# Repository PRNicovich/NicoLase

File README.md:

# NicoLase 

## An open-source diode laser combiner, fiber launch, and sequencing controller for fluorescence microscopy

New users please check out the associated open-access publication from PLoS ONE:
http://dx.doi.org/10.1371/journal.pone.0173879

Therein you'll find a complete description of the NicoLase platform and performance specifications.  

Here in the repository you can find all of the files and supplementary descriptions to build your own fiber-coupled diode laser launch as described in the publication. As the project matures, new features and softwares will be incorporated here.  

### Motivation
Diode laser units are convenient for fluorescence microscopy and super-resolution microscopy due to their high power and ease of use.  A couple dozen lines are avaliable from most makers to cover UV through mid-IR applications.  With the addition of direct modulation avaliable on nearly all modern units there's no need for an AOTF or other tuning or power modulation control in addition to the diodes themselves. 

Multiple laser lines are almost are a requirement for a modern fluorescence microscope.  Rarely can a system produce publication-appropriate results without at least a second laser.  Multiple lasers need to be combined and then controlled together for multicolor illumination.  

Software and trigger control of the lasers is strongly desired.  Microscopy cameras often have a dead time between frames when laser illumination is (almost always) undesired, and at the very least it's nice to have a laser that shuts off when the acquisition simply isn't running. Then, as a further step, it's often necessary to alternate or otherwise sequence lasers for certain experiments (*ie* ALEX FRET or pseudo-simultaneous multicolor imaging).  With digital control of laser emission this needs to be controlled at the laser head. 

There are commercial options to achieve nearly all of these.  Basically, this system does not do anything you can't buy.  But the final cost here is 2/3 to 1/2 of the cost of commerical instruments and can be easily customized in terms of size, number of lines, and final configuration.  The system here is cheap (ish), flexible, and quite compact. 

Two generations of this project are included in the repo.  The first, half-sarcastically called the NicoLase 1500, is a single-mirror coupling system running 5 (expandable to 6) diode lasers.  The later, the NicoLase 2400, is a two-mirror system with 4 diode lasers.  These share the same footprint, many of the same components, and the same control software and PC interface.  

Note: Throughout I use the catch-all term 'lasers' or 'laser outputs' for the end target for TTL outputs of the controller.  Of course this same controller and software can be used with any equipment receiving a TTL input pulse that needs to be synced to camera acquisitions.  We commonly use an LED illuminator for transmitted light with the controller output, for example. 

### Hardware
#### Lasers
The NicoLase is built primarily around Vortran Stradus laser diode units.  These are a standardized size for each line, reasonably priced, and produce a large amount of power for their size and cost.  Nearly all produce enough power for dSTORM work.  These units can be digitally modulated at a high rate (usually up to 2 MHz) and potentially analog modulated if desired.  I don't have any financial reason for recommending these units, just a satisfied customer.

A straightforward modification allows you to use Coherent OBIS heads in place of some/all of the Vortran units.  Control is nearly identical and aside from some extra screw holes, these are drop-in replacements for the Vortran units. 

I haven't had a chance to test any other laser diodes with this system, though there's no reason others with the same characteristics won't work.  

Key features for any lasers chosen are :  
-  100 mm x 50 mm footprint or smaller
-  19.05 mm or 3/4" beam height, or can be brought to this height with spacers/lifts
-  Digital modulation via TTL pulse
-  Software control of laser power via USB or RS-232 (for add-on plug-in control)

#### Heatsinks and Mounting
Diode laser heads require a heat sink for proper operation, which has to at least be a contact with a block of aluminum.  We need the laser outputs to be at 39.0 mm to intersect with the steering and coupling optics.  Oh, and the laser have to actually bolt down to something. 

To solve these issues, a heat sink + mounting block was machined.  Three dimensions must be held to strict tolerances for this part.  The top must be as flat as possible (0.1 mm specified) with no scratches or machine marks to interface with the bottom of the laser diode for heat transfer.  The top and bottom faces must be parallel (0.1 mm specified) so the beams are at the same height.  And the total height must be the specified thickness (0.2 mm specified).  

Keeping the top flat can be done by using a piece of ground stock and machining other faces.  Keeping the top and bottom flat to that tolerance should be straightforward for a decent mill.  And we can use a bit of a trick for the total height.  This is because we don't actually care about the bottom of the part and can therefore add shims of sheet stock (with clearance holes cut) to bring the total assembly to the desired height.  The block can be machined on the bottom face until the thickness is a bit short, then a piece or pieces of sheet stock selected to bring it up to the final thickness.  Much simpler and easier to meet the necessary tolerance than hitting the right thickness with machining only.  

The heat sink block must be made of either aluminum or copper.  Steel, especially stainless, does not have a sufficient heat transfer rate to keep the diodes from overheating.  We had our top blocks made from aluminum and the shims from copper sheet, which works great. DO NOT add heat sink paste or thermal grease to the interface between the laser and the heat sink block.  That stuff outgasses like mad and gets on your optics, plus the flat surface does an excellent job of heat transfer already. 

Mirrors and other optics mount to standard Thorlabs parts except for the fiber coupler itself.  This needs a custom pedistal to be machined, but this is a straightforward piece of turning.  No dramas there.  The original 1500 design uses a flat block for this mount but the 2400 pedistal is a much better design. 

All optics are chosen for a 1.5" center height.  Mirrors and dichroic mirrors are mounted in Thorlabs Polaris 1" mounts.  The single-mirror system requires 3-adjuster mounts, but either 2- or 3- adjuster mounts can be used for the two-mirror system.  Hex adjuster are nice for squeezing the mounts closer together, but are a bit more of a pain to adjust.  Clearances are just barely there for thumb adjusters and for your fingers. Those more rotundly-digited of us may prefer the hex adjuster mirrors.  

Excitation filters can be mounted in standard lens mounts, or options for 3D printed mounts for 1/2" filters designed for the NicoLase is given in my 3D printing repo [here](https://github.com/PRNicovich/3D-Printed-Optics-Lab-Parts).  A mount to tie the Aruino to the optical table is given in the same repo, or you can make a mounting plate to bolt in a spare laser slot on the heat sink block (3D printed version forthcoming).  

Drawings and pictures of enclosures are provided (one a bit more 'polished' than the other).  These keep the lasers away from the unsuspecting eyes of users and the optics protected from bumps and dust.  Components for the NicoLase 1500 enclosure are from 80/20 using 25 mm aluminum profile.  The 2400 enclosure is made of corrugated plastic sheeting and held together with magnets and 3D printed magnet clips (available [here](https://github.com/PRNicovich/3D-Printed-Optics-Lab-Parts/tree/master/Magnet%20Clips)).  In both cases the laser power supplies are on the optical table with the breadboard and lasers above, but there's no reason the whole assembly can't be moved to a shelf off of the optical table if you need the space.  

**Update April 2019** - Plans for an enclosure in the form factor of a 19" rack (that fits under the optical table!) is included in 3600 model folder.  This rack can hold the NicoLase breadboard in the upper compartment with additional accessories and equipment underneath. This includes laser power supplies (on their own shelf) with any additional boxes, power supplies, or even a PC underneath.  Laser portion can be enclosed for a facility or dark room application.  Whole thing sits on sliding feet to fit under the optical table making a very convenient package! 

Technical drawings for all machined components are given.  These were sufficient for our Uni's machine shop to complete satisfactory work with no additional consultation.  

#### Optics
Optics are relatively straightforward - a few dichroic mirrors, optional filters, and a fiber coupler.  This unit is built around mostly standard Thorlabs components.  Aside from a T-shirt I got at a conference once, I have no interest in pushing Thorlabs components though they are reliable, self-compatible, and widely available. 

Dichroic mirrors are used to combine lasers into a single multi-wavelength beam.  A mix of Chroma and Semrock filters are used.  All are standard 1" round long-pass filters costing a few hundred USD each.  Which ones are used depends on which wavelengths are being combined, but of course you want to pick a cut-on wavelength that reflects the beam being folded in and transmits all others upstream.  Picking a cut-on wavelength that falls between adjacent laser lines usually works well, but double-check the provided spectra to confirm there aren't odd peaks or dips in the filter spectrum.  

Diode lasers often require an emission clean-up filter to block odd long-wavelength emission from the laser head.  We've had particularly bad luck with 488 nm diodes in this sense.  At the same time, diode heads are ordered by nominal wavelength, but the actual wavelength of the supplied unit may vary 3-5 nm from this nomial value.  This means that you can't necessarily order a laser line filter for the nominal wavelength and have it work for your diode.  For example, our '488' nm diode actually emits at 490 nm, and our 488 nm clean-up filter blocks half of the emitted power.  A 485/10 band-pass filter does a much better job and blocks the offending green emission.  This means you MUST double-check the actual emitted wavelength (should be specified by the vendor in the factory testing docs) when chosing an emission filter or if emitted wavelength is critical. 

A Thorlabs PAFA-X-F-A Achromatic FiberPort FC/APC coupler is used to couple the combined laser beams into a polarization-maintaining FC/APC patch cable.  The FiberPorts aren't cheap (~$500 USD), but they do prove to be stable and relatively achromatic.  50-70% coupling efficiency across all lines is achievable without too much hassle on this configuration.

A bill of materials for optical components is given in the Hardware folder of the repo.  

A procedure for the assembly and alignment of the optics has also been included in the Hardware\Optics\ folder of the repo.

###### One mirror or two?
Using two mirrors to steer a beam from one vector to another is taken as dogma for most applications. It is true that this is necessary for arbitrary output and input vectors, but that's not the case here.  

Because lasers with identical beam heights and angle relative to the breadboard are used (assuming proper machining tolerances on the mounting block), one degree of freedom is removed. As such you don't need four adjusters to steer the beam into the fiber coupler, but rather three.  This means that you can use a single three-adjuster mirror mount and, as a result, squeeze 6 laser heads and steering optics into a single 450 mm x 300 mm footprint.  Alignment of a single-mirror system is only marginally more difficult than aligning the two mirror system. This layout is given in the NicoLase 1500 description.  

A more typical two adjuster layout is used in the NicoLase 2400.  This uses a pair of two-adjuster mirrors for each laser and fits four lasers into the 450 mm x 300 mm footprint.  Using two mirrors does have more tolerance for lasers that might have unequal beam heights, such as when mixing Vortran and OBIS diode heads in a single unit. 

**Update April 2019** - A new, improved, 6 head version included as NicoLase 3600.  This combines the loads of lasers in the 1500 (plus an one more!) with the ease of alignment of the 2400.  The use of new Thorlabs 12 mm posts and 1/2" optics squeezes an additional mirror path in the same footprint as the other NicoLase designs.  The resulting design is easier to align and support combinations of laser makers who might have slightly different opinions on what a 3/4" beam height actually is.  This breadboard design is also a bit taller (1.6" inches vs 1.5"; 39.3 mm vs 38.1 mm) with a to avoid the need of any additional custom-made mounting components beyond the heat sink.  This combined with the new rack mount enclosure is a compact, easy to align, integrated solution for your microscope hardware. 

An additional 5-head version of the heat sink is included (NicoLase 3500) that allows additional beam conditioning or steering accessories to be included on the breadboard.  Like the 3600, there is a 39.3 mm beam height, dual mirror alignment on the fold-in lines, and fits well in the 19" rack style enclosure.

Special thanks to Mike Taormina for the clever design.

#### Controller
Trigger translation, especially with a time-variable component, requires some form of controller.  A DAC board (such as the many options from National Instruments) are the "professional" choice, but are frankly overkill.  A couple of input channels and no more than 8 input channels are needed. Timing precision, rise times, and trigger jitter on the microsecond or even tens of microseconds time scale is actually more than good enough here (10 microseconds of jitter on a 10 ms exposure is a 0.1% variation). USB or serial control is good to communicate with the controller,  as is low cost for the unit and the I/O interface.

Enter the Arduino Uno.  Units cost $40 AUD for an official one (knock-offs are under $10).  Timing precision and programming space is sufficient, I/O interfaces are easy with a shield, and there's a USB serial port built-in.  

Another Arduino variant or another microcontroller can be swapped in if the need arises (maybe you want to add more analog ins/outs? or a 32 bit timer?) but that's beyond the scope of this project.  As long as you can take a master trigger in, output the appropriate pulses, and communicate over a serial port, this part can be modified to meet your needs.

Interfacing with the trigger pulses in and out is accomplished with a custom shield.  The PCB includes 10 BNC ports (2 camera inputs, 2 camera outputs, and 6 laser outputs), a OR gate, 3v3 to 5v level shifter, and pushbutton, plus a few pull-down and limiting resistors.  With some male header strips, the shield mounts atop the Arduino.  

Circuit schematic included in ShieldPCB folder.  All power is drawn from Arduino.  PRIMARY TRIGGER camera input heads straight to SECONDARY TRIGGER output as well as to a 3v3 OR gate.  Other OR gate input is SECONDARY FIRE input, meaning either camera can be used to trigger Arduino.  OR gate output connects through 4050 3v3->5v level shifter to ensure that pulse adequately triggers 5v input on Arduino.  There the 5v pulse connects to interrupt digital pin 2 of the Arduino.  Arduino digital pin 3 connects to pushbutton on PCB which can also be used to iterate laser sequence for testing in place of a camera trigger.  Digital pin 4 goes through a current-limiting resistor to the PRIMARY TRIGGER output. 

All CHX outputs occur on Analog Out register of Arduino.  Sharing a register means all can be set simultaneously in the Arduino software without having to go through the digitalWrite() function.  This allows faster triggering and all lasers are set with the same delay/jitter rather than a variable delay depending on which pin on the register they lie.  

The shield PCB can be ordered [here](https://dirtypcbs.com/store/designer/details/8887/5815/nicolase-arduino-shield-v2-1).  If you order there I get a dollar or two of shop credit, but you're welcome to take the files in this repo and order them from another supplier.  A bill of materials is also included in the Shield repo for the parts necessary to populate the shield.  Surface mount components are used to get everything squeezed into the space available.  These may be small but they can be successfully hand-soldered using a standard temperature controlled soldering iron and reel solder.  A great guide for those getting started with surface mount components is available from SparkFun (https://www.sparkfun.com/tutorials/36). All should be commonly available from standard suppliers (element14, Mouser, DigiKey...) though I haven't done any work to ensure the longevity of the supply chain for any specific component.

### Software
Software is split into two parts - controller software running on the Arduino and interface software for the PC.  Only the controller software is strictly necessary for triggering.  Examples of PC software are given which can be expanded to work with your particular system.

###### Controller Software
The Arduino sketch accomplishes two primary needs - external communication and sequence programming via serial port, and triggering + interating a programmed laser sequence in response to a trigger pulse.  

Serial commands are via the USB connection to the control PC.  This USB also provides power to the Arduino, so no additional external supply is required.  Once powered on, the Arduino listens over the serial port for an incoming sequence to alter the standard sequence (all lasers on when the fire signal is high) or to reach any of the alternate features.  

A detailed description of the possible serial commands is given in the documentation in the Arduino Sketch folder of the repo.  Breifly each command is a capital letter character, sometimes a space followed by one or more digits, and a newline character.  

A Basic Controller and an Advanced System Controller are included in the repo.  The Basic Controller relies on an external trigger signal (ie a camera Fire pulse) to synchronize and iterate over the sequence of outputs.  The Advanced System Controller provides the main features of the Basic Controller in external clock mode, but additionally can be configured to have the Arduino act as the master clock for the system. 

The Basic Controller is simpler to operate and is sufficient for most applications.  The Advanced System Controller is a great option if you wish to have a master clock that isn't reliant on the camera signal.  Additionally, the Advanced System Controller solves the timelapse issue in Micromanager for acquisitions between ~3 Hz and the free-run rate of your camera.  More detail on this issue is given below.

Both configurations use the same hardware and share many of the same serial commands. Switching between the two options is a matter of uploading the appropriate sketch to the Arduino and intefacing with the respective PC-side software or serial commands.

###### Basic Controller

Triggering (via either the PCB PIMARY FIRE or SECONDARY FIRE connection) triggers an interrupt on the Arduino. A rising edge causes the laser outputs (CH1 through CH6) to go high.  A falling edge on the trigger pulse drives the laser outputs low and iterates the programmed sequence to the next one.  If the end of the sequence list is reached the Arduino goes back to the start.  Any given line of the sequence can be repeated any number of times (up to 2147483647 times per line).  

Alternate functions are available for what is called a pre- or post-acquisition command.  These are single laser patterns that can be triggered by a serial command independent of a trigger input.  Each has a time associated for how long the outputs will be held high.  The pre-acquisition sequence has an additional delay after which an optional pulse will be send to the PRIMARY TRIGGER pin.  This means you can, for example, have an acquisition sequence of a 488 nm laser and 561 nm laser firing on alternating camera frames (the 'acquisition sequence').  Before that sequence is reached, however, a pre-acquisition sequence of a 405 nm laser is fired with no camera acquisition for 1000 ms, followed by a 500 ms delay, and then the actual acquisition begun by the Arduino sending a pulse to the primary camera.  A more detailed description of the 
triggering and associated controller functions is given in the Triggering section.  

Additional commands enable configuration of the controller as a UserDefinedStateDevice and UserDefinedShutter device in Micro-Manager.  In this mode basic fluorescence microscopy functions (select a laser set and toggle on/off) directly through Micro-manager GUI.  For those wishing to use the NicoLase in a straightforward or multi-user environment this may be useful. 

###### Advanced System Controller

The basic controls for laser sequencing during a camera-synchronized acquisition described above are supported.  In addition there is an available mode in which the Arduino can act as the master system clock.  The camera and lasers are then both driven by the Arduino system clock.

The primary motivation for the Arduino as the master clock is solving the no-mans-land of timelapse rates between the camera's free-run rate (delay < [exposure time + dead time]) and ~3 Hz.  In Micromanager, the timelapse delays in this range seem to change from a continuous camera acquisition to a series of single acquisitions at a given rate.  This comes with much more communication overhead, ultimately limiting the capture rate to accomodate the ~250 ms of added delay. Such a delay is not immediately obvious in the software without checking the timestamps of acquired images and may not necessarily affect your system or measurements. We like to work in the affected range for our system, however, so a solution is needed.  

In this configuration all cameras are set to External Trigger mode.  The primary camera is then triggered by the Arduino.  If a secondary camera is present, it is triggered by the Fire signal from the primary camera.  By having all cameras set to External Trigger mode, the communication overhead comes once at the beginning of the acquisition.  Between frame captures the camera does not have to communicate with the PC except to transfer image data.  The cameras wait for the next incoming external trigger pulse to take the next image and are able to capture without additional communication overhead.  This means timelapse images can be captured at any rate from the free-run rate of the camera on up to a limit imposed by the Arduino timing roll-over (days to weeks).  

It is essential that these external pulses come when the camera is listening, so the external delay must be greater than the set exposure time plus the camera dead time (50-65 ms on an Andor 888; check the Minumum Cycle Time on the Micromanager Device Property Browser for this value).  The current version of this software does not check for a 'Ready' signal from the camera before sending the next pulse, so this timing is the responsibility of the user. 

** Note ** 
With the Arduino as the master clock, you don't need another clock signal!  If you simply want to trigger TTL devices at a given rate, then this software may work for you!  See .\Software\AdvancedSystemController\Arduino_controller documentation for details on how to control sequencing and serial communication with the associated Arduino sketch.

###### PC Software
Communication with the Arduino is through standard serial commands.  Serial settings are essentially defaults - 9600 baud, 8-n-1, and a newline character line feed.  

The Arduino is added to the Micro-manager config as a FreeSerialPort device (be sure to get the right COM port + settings!) for this communication.  sendSerialPortCommand() calls pass along strings to the Arduino at the beginning of the experiment (or during, if you want) which then waits for trigger pulses from the camera.  

For the Basic Controller an example Micro-manager script to communicate laser sequence settings are given for inclusion into the Beanshell interface.  A MATLAB GUI for easily uploading arbitrary sequences is also included.  This can run in parallel with Micro-manager if the FreeSerialPort has NOT been added to the Micro-manager config, or in your own external application. 

A Micro-manager plug-in for the Advanced System Controller includes a GUI for programming laser and camera sequencing as well as loop and step timing.  The configuration is passed to the Arduino via serial commands and the acquisition sequence begun.  The plug-in then reassembles the data sequence into the proper multidimensional stack, including separating channels by camera and laser configuration dimension.  

**Update March 2019** - The Basic Controller now supports use as a SerialStateDevice and SerialShutter in MicroManager.  This allows you to control the laser sequencer just like a physical shutter or filter wheel.  See the software build notes for details.

**Update May 2020** - Basic controller sketch can now be controlled via the nicoLase Python class.  Package is in ./Software/BasicController/Python.  Run "pip install -e ." with terminal pointed to that directory to install. 

### Triggering
A diagram of the triggering sequence in the default external clock mode is given below:

Here input signals are blue (Primary In and Secondary In), outputs to cameras in red (Primary Out and Secondary Out), and outputs to lasers in wavelength-approximate colors (Ch6 - Ch1).  Trigger event stages are separated by dashed black lines with acquisition frames in gray blocks with gray dotted borders.

Because the SECONDARY FIRE and PRIMARY FIRE inputs first pass through an OR gate, either being high results in the input to the Arduino being high.  In practice the separation between these two pulses is on the order of single microseconds, so these are treated as simultaneous.  Also, this means that even in a dual-camera system, running either camera alone is sufficient to trigger the CHX outputs.  Single cameras can work on either, though using PRIMARY TRIGGER input only is recommended.

The progression of trigger signals for this experiment of 8 imaging frames is as follows:
-  Serial command to Arduino starts Pre-acquisition sequence with Ch1 and Ch6 high (ie 405 nm laser and blue transmitted LED)
-  After defined illumination time, Pre-acquisition ends and Pre-acquisition delay begins
-  After defined pre-acquisition delay time, a pulse is sent to the PRIMARY TRIGGER output
-  The Primary camera begins acquiring frames (charcteristics defined through camera software).  Each is associated with an input pulse at the PRIMARY FIRE pin
-  Each incoming PRIMARY FIRE pulse results in an output SECONDARY TRIGGER pulse and output pulses to the user-specified CHX output pins.  Here I show alternating sequences of [Ch5 + Ch4] and [Ch3 + Ch2] to illustrate the programmable sequencing of these pins. 
- Each SECONDARY TRIGGER pulse triggers the secondary camera, which in turn results in an incoming SECONDARY FIRE pulse (ignored in 2-camera acquisitions)
- Falling edge of PRIMARY FIRE pulse drives CHX outputs low and Arduino iterates to next line of sequence
- After acquisition is complete, serial command to Arduino starts Post-acquisition sequence (here Ch6, blue transmitted LED high) for user-defined time

With the Arduino as the master clock, the primary camera follows trigger pulses from the Arduino.  The secondary camera, if present, follows the primary camera.  For each frame the PRIMARY TRIGGER pin on the Arduino is used to trigger the primary camera, which is in External Trigger mode (rather than External Start or Software triggering).  The Advanced Laser Controller software does not explicitly support a Pre- or Post-acquisition exposure at this time.

Outgoing pulses are all 5v TTL.  Incoming signals are anticipated to be 3v3 TTL signals (5v tolerant).  

Typical configuration assumes that CHX outputs are connected to lasers from Ch1 -> Ch6 running blue-red.  This is arbitrary except for keeping things straight in associated PC software.

### Going foward
As these systems continue to be used and mature more modifications and software will be added to the repo.  Until then, feel free to ask questions or give a build of your own a try.

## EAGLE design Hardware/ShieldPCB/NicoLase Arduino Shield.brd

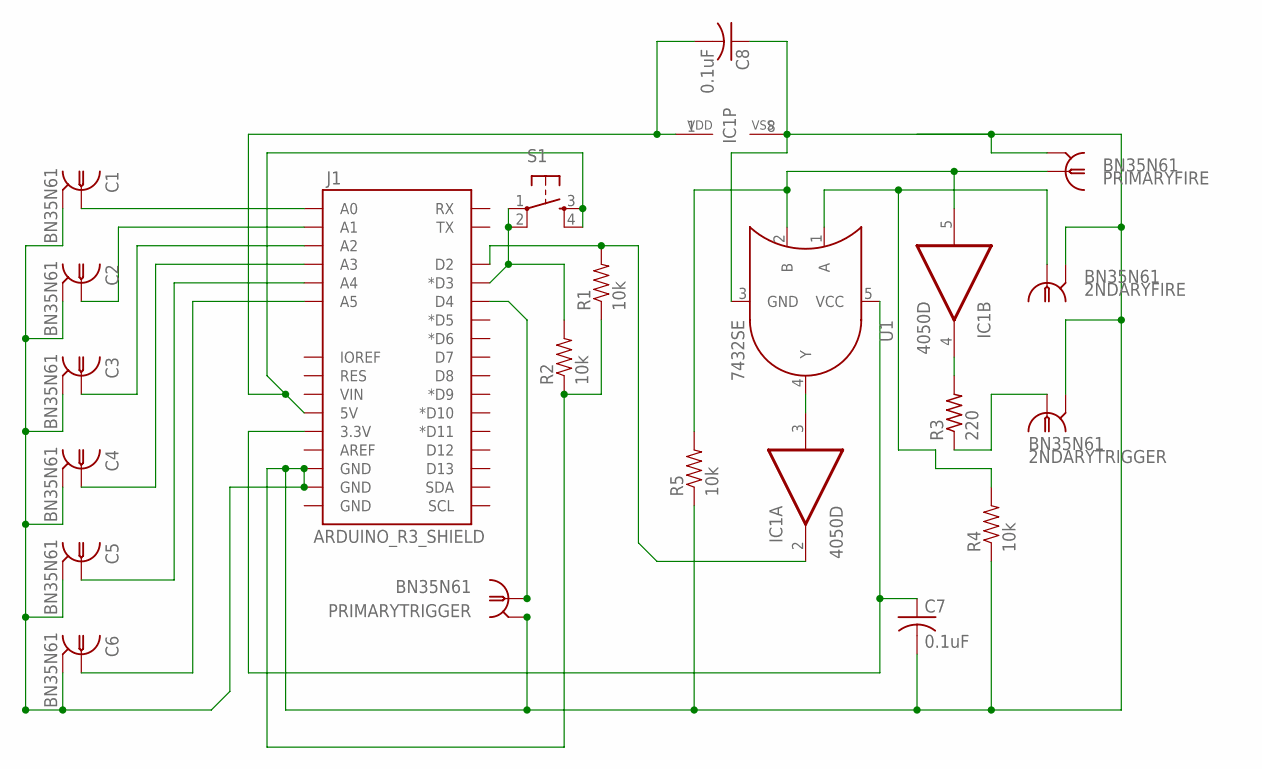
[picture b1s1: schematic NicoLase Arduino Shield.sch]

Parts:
2NDARYFIRE, 2NDARYTRIGGER: BN35N61; B35N61
C1, C2, C3, C4, C5, C6: BN35N61; B35N61
C7, C8: 0.1uF; C1206
IC1: 4050D; SO16
J1: ARDUINO_R3_SHIELD; UNO_R3_SHIELD
PRIMARYFIRE: BN35N61; B35N61
PRIMARYTRIGGER: BN35N61; B35N61
R1, R2, R4, R5: 10k; 1206
R3: 220; M1206
S1: TAC_SWITCHPTH; TACTILE-PTH
U1: 7432SE; SOT353

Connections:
GND: 2NDARYFIRE.2, 2NDARYFIRE.3 (2), 2NDARYFIRE.4 (2), 2NDARYFIRE.5 (2), 2NDARYTRIGGER.2, 2NDARYTRIGGER.3 (2), 2NDARYTRIGGER.4 (2), 2NDARYTRIGGER.5 (2), C1.2, C1.3 (2), C1.4 (2), C1.5 (2), C2.2, C2.3 (2), C2.4 (2), C2.5 (2), C3.2, C3.3 (2), C3.4 (2), C3.5 (2), C4.2, C4.3 (2), C4.4 (2), C4.5 (2), C5.2, C5.3 (2), C5.4 (2), C5.5 (2), C6.2, C6.3 (2), C6.4 (2), C6.5 (2), C7.2, C8.1, IC1.7 (I), IC1.8 (VSS), IC1.9 (I), IC1.11 (I), IC1.14 (I), J1.GND@1 (GND), J1.GND@2 (GND), PRIMARYFIRE.2, PRIMARYFIRE.3 (2), PRIMARYFIRE.4 (2), PRIMARYFIRE.5 (2), PRIMARYTRIGGER.2, PRIMARYTRIGGER.3 (2), PRIMARYTRIGGER.4 (2), PRIMARYTRIGGER.5 (2), R1.1, R2.1, R4.1, R5.1, U1.3 (GND)
unnamed: C7.1, J1.3.3V, U1.5 (VCC)
unnamed: C1.1, J1.A0
unnamed: C2.1, J1.A1
unnamed: C3.1, J1.A2
unnamed: C4.1, J1.A3
unnamed: C5.1, J1.A4
unnamed: C6.1, J1.A5
unnamed: IC1.3 (I), U1.4 (Y)
unnamed: 2NDARYTRIGGER.1, R3.1
unnamed: J1.D3 (*D3), R2.2, S1.1, S1.2
unnamed: IC1.4 (O), R3.2
unnamed: C8.2, IC1.1 (VDD), J1.5V, S1.3, S1.4
unnamed: IC1.2 (O), J1.D2, R1.2
unnamed: J1.D4, PRIMARYTRIGGER.1
unnamed: 2NDARYFIRE.1, R4.2, U1.1 (A)
SLAVEFIRE: IC1.5 (I), PRIMARYFIRE.1, R5.2, U1.2 (B)

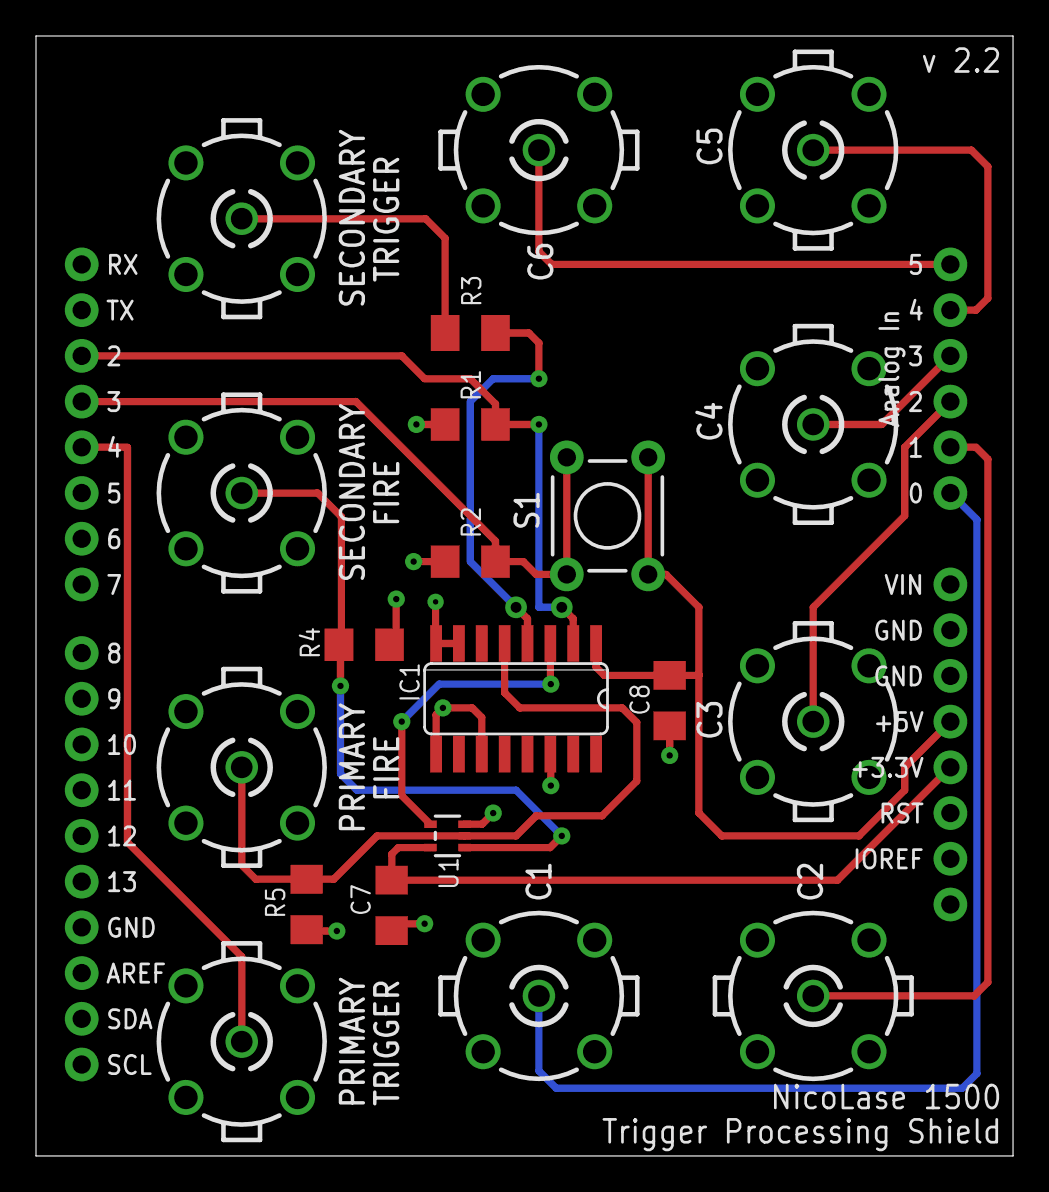
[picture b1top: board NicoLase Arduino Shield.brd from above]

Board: 2 copper layers, 54.3 x 62.2 mm, 21 parts (0 on the bottom side), 17 nets.

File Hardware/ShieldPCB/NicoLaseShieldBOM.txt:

Partlist for NicoLase Arduino Shield

Assembly variant: 

Part          Value             Package       

C1            BN35N61           B35N61        
C2            BN35N61           B35N61        
C3            BN35N61           B35N61        
C4            BN35N61           B35N61        
C5            BN35N61           B35N61        
C6            BN35N61           B35N61        
IC1           74HC4050D         SO16          
J1            NicoLaseShieldPCB CustomPCB
MASTERFIRE    BN35N61           B35N61       
MASTERTRIGGER BN35N61           B35N61        
R1            10k               1206          
R2            10k               1206          
R3            220               1206
R4	      10k               1206     
R5            10k               1206              
S1            NormOpenPshBtn    TACTILE-PTH   
SLAVEFIRE     BN35N61           B35N61        
SLAVETRIGGER  BN35N61           B35N61       
U1            7432SE            SOT353       

Add sufficient male 0.1" headers to populate board (28 total). 

BNC sockets (BN35N61) are these are equivalent:
http://au.element14.com/webapp/wcs/stores/servlet/ProductDis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

The OR gate (U1) used in implementation is 74HC1G32GW from NXP.  Important characteristics are CMOS logic levels (3v3), can run on 3v3 input power, and SOT-353 footprint.  

Files in NicoLaseArduinoShield.zip can be forwarded to your favorite PCB house for manufacture.

Surface mount parts are chosen for a compact assembly.  While small, these have been successfully assembled using a standard temperature-controlled soldering iron and reel solder.  For those starting out with working with surface-mount parts, an excellent guide is available from SparkFun at https://www.sparkfun.com/tutorials/36. 

Edit added 12/12/2016 - The inputs to the OR gate require pull-down resistors for proper operation, especially if either is left unpopulated in the final assembly.  These have been added to the PCB design as R4 and R5.  10k ohm is appropriate for both.

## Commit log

2016-06-26 Initialize repo.
2016-06-26 Create License.MD
    Added license file.
2016-06-26 Create NicoLaseReadme.MD
    Convert readme to display in repo homepage
2016-06-26 Delete NicoLaseReadme.MD
    Try readme again...
2016-06-26 Create README.md
    Readme formatted for splash page
2016-06-26 Cropped render image files.
2016-09-15 Added Dual output files Updated Optics files and added 12.5 mm adapter drawing. Renamed HCP Pedistal drawing file
2016-09-15 Updated build notes and readme.
2016-11-30 Arduino sketch missing critical interrupt lines. These have been added.
2016-12-12 Updated PCB to include pull-down resistors on both inputs of OR gate.
2016-12-12 Updated PCB to include pull-down resistors on both OR gate inputs.
2017-01-16 Enclosure BOMs, drawings, and readmes added.
2017-01-16 Updating dimensions drawing.
2017-01-16 Added STEP files for heat sink mounts.
2017-01-17 Updated build notes and readme with surface-mount soldering guide.
2017-01-22 Added alignment guide pdf.
2017-01-27 Update NicoLaseShieldBOM.txt
    Added description of OR gate part and number.
2017-01-31 Fixed error in trace of MASTERFIRE on PCB. .brd file updated. Removed Gerber files as they are incorrect, but not able to re-generate at this time.
2017-02-27 Added software and descriptions for Advanced Laser Controller. Previous software components moved to .\Software\BasicController\
2017-03-16 Update readme with manuscript link
2017-11-03 Updated link to better PCB design.
2018-06-04 Updated basic controller to allow direct writing to specific output pins via serial communication.
2019-03-14 Updated basic controller sketch. Added mode to clear and append single line to sequence. Added mode to toggle first sequence on and off over serial, ignoring interrupt state. Added terse echo of sequ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
2019-03-14 Updated toggle on over serial mode to detach interrupt from trigger when called. Must call 'X' to reset interrupt mode.
2019-04-06 Added Micro-manager configurations to demo State Device and Serial configurations. Updated readme files to include these features.
2019-04-18 Added files for 3600 model. Includes enclosure files, heat sink, and updated Readme.
2019-04-18 Update README.md
    Added acknowledgement for Mike.
2019-05-03 Delete NicoLaseReadMe.txt
    Redundant with readme.md and deprecated.
2019-05-03 Update README.md
    Added note about serial state device and shutter device to readme.
2019-12-18 Add 3500 heat sink block.
2020-01-02 Added heat sink block drawing for 3500 design.
2020-01-02 Create README.md
    Add readme for heat sink block folder.
2020-03-10 Added heat sink for 3200.
2020-03-11 Added version return command to SerialSequencingUploader.ino sketch
2020-03-25 Corrected typos in SerialSequenceUploader sketch.
2020-04-15 Adding Python class and demo.
2020-04-15 Add .gitignore file.
2020-04-20 Update README.md to include mention of Python class and demo.
2020-04-20 Moving folders to fix display thanks to case sensitivity.
2020-04-20 Adding back in Python folder with proper case.
2020-05-16 Made Python package and setup.py for NicoLaseDriver.py.
2020-05-16 Updated README to mention now-included Python class
    Added mention of Python driver class to README file.
2020-05-16 Cleaning up after merge w/ setupPython.
2020-06-06 Added ground plane and corrected minor layout issues.
2020-06-06 Added 0.1uF capacitors on power rails. Correcter minor schematic issues.
2020-06-06 Updated top silk.
2020-06-06 Updated the production files.
2020-06-08 Review filcarv pull request. Update silkscreen and README terminology for primary/secondary fire/trigger lines.
2020-06-08 Replace a couple more occurances of terminology change in readme file.
2020-06-08 Grounded the non-used gates.
2020-10-16 Updated ShieldPCB BOM with manufactor part numbers.
2020-12-16 Update NicoLaseShieldBOM.txt
    Included erroneous line about R1-R16. Updated to remove.
2020-12-16 Update NicoLaseShieldBOM.txt
    Adding in capacitors in latest version of board
2020-12-21 Add '? P' command to query for proceed trigger. Can have Arduino listen for TTL proceed pulse then respond to query over serial later.
2020-12-21 Move proceedTrigger = true; flag set to deal with interrupt setting to true on startup.

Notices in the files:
parts and their libraries:
SparkFun-Boards: Licensing: Creative Commons ShareAlike 4.0 International - https://creativecommons.org/licenses/by-sa/4.0
